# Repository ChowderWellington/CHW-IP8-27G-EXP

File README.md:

# CHW-IP8-27G-EXP
An open source inkjet color printer with a nozzle built from the ground up!
<div align="center"></div>

(Chowder Hardware Works-Inkjet Printer 8 Nozzle-27 gauge precision nozzles-experimental)

Printhead: PX8-20H-01

Manufacturer: Chowder INC

DPI: 1.5

yes i love naming things annoyingly

## Overview
The CHW-IP8-27G-EXP is an inkjet color printer that can print at really bad dpi! But it does work! and i'm not using other people's nozzles, as I built my own from scratch!

## Features
- Very replaceable (you can 3D print any non-electrical parts and to get replacements for any electrical stuff is very cheap!)
- Custom Nozzle

# Full CAD

Here are the .stp files (THEY NEED TO BE PRINTED SEPARATELY) because stardance doesn't like .stl's

[Nozzles+Manifold](https://github.com/ChowderWellington/CHW-IP8-27G-EXP/blob/main/cad/Main%20Nozzle%20Setup%20V4.5%20%2B%20Manifold.stp)

[Printhead](https://github.com/ChowderWellington/CHW-IP8-27G-EXP/blob/main/cad/Main%20printhead%20V1.stp)

If you would like to recreate what I have done, use these files, or check out the .stls below if you would prefer them

[Nozzles+Manifold](https://github.com/ChowderWellington/CHW-IP8-27G-EXP/blob/main/cad/Main%20Nozzle%20Setup%20V4.5%20%2B%20Manifold.stl)

[Printhead](https://github.com/ChowderWellington/CHW-IP8-27G-EXP/blob/main/cad/Main%20printhead%20V1.stl)

## Replacing parts (part of the Full CAD)

I know a lot of the parts may break, especially the nozzles which can be faulty, but you should be able to find replacement bits for almost anything below. These are all in stl format btw.

[Single Lid for nozzle](https://github.com/ChowderWellington/CHW-IP8-27G-EXP/blob/main/cad/Main%20Nozzle%20Setup%20V4.5%20Lid%20Single.stl)

[Single Tank for nozzle](https://github.com/ChowderWellington/CHW-IP8-27G-EXP/blob/main/cad/Main%20Nozzle%20Setup%20V4.5%20Tank%20Single.stl)

[Main Printhead](https://github.com/ChowderWellington/CHW-IP8-27G-EXP/blob/main/cad/Main%20printhead%20V1.stl)

[Manifold](https://github.com/ChowderWellington/CHW-IP8-27G-EXP/blob/main/cad/Manifold%20V1.stl)

## Older Models (part of the Full CAD)
Older models of most of the parts can be found in the [cad folder](https://github.com/ChowderWellington/CHW-IP8-27G-EXP/tree/main/cad). However, it is NOT recommended to use them. Please use the newest model (V4.5 for the nozzle, V1 for the printhead and V1 for the manifold). 

## How to print the printer (part of the Full CAD)

1. Download the relevant files from the model files section above
2. Print it on any 3D printer using supports. For the nozzle and the manifold, it should only generate supports for the piping. Not inside it. For the printhead, there should be no supports.
3. Assemble using the guide (W.I.P)

This project was fit for a Bambu Labs A1 Mini, and a 0.4MM nozzle, but I assume it will work on anything else.

## Technical details

The PX8-20H-01 contains 8 piezoelectric discs that move forward and backwards under high voltage, causing a membrane to push a tiny ink droplet out onto a page, hence the name - inkjet. A motor in the CHW-IP8-27G moves the PX8-20H-01 back and forth, meaning it can print anywhere on a page using its nozzles. It is 1.5 DPI 

## Model Names
- CHW-IP8-27G-EXP - Full printer assembly (Printhead, nozzles, feeders etc)
- PX8-20H-01 - Experimental nozzle (Newest model)

## Datasheets
- [PX8-20H-01](https://github.com/ChowderWellington/CHW-IP8-27G-EXP/blob/main/assets/PX8-20H-01%20DATASHEET.pdf)

## Logo

The logo was designed by me, and it has a pretty cool story! 

I was originally going for a cool spiral sort of logo, where i made a bunch of circles that get increasingly smaller and change between black and white, but in canva, I highlighted the centre circle, and noticed that the select box looked warped for some reason. It reminded me of [this](https://raw.githubusercontent.com/ChowderWellington/CHW-IP8-27G-EXP/refs/heads/main/assets/cafe-wall-big.gif) optical illusion so i just stuck with it, and now it is the logo!

## PCB
You can order the pcb from anywhere, but [here are the files you'll need](https://github.com/ChowderWellington/CHW-IP8-27G-EXP/tree/main/pcb)

You actually don't need most of these, just [the gerber files](https://github.com/ChowderWellington/CHW-IP8-27G-EXP/raw/refs/heads/main/pcb/Gerber_PX8-20H-01_PCB_PX8-20H-01_2026-08-30.zip) for manufacturing. To buy the parts you'll need to solder on to the board, check out the [BOM.csv](https://github.com/ChowderWellington/CHW-IP8-27G-EXP/blob/main/BOM.csv)

## Extra thanks!
- Thank you so much to stardance for funding whatever this is! Y'all are the best!! Please keep doing what you're doing, and everyone WILL enjoy it! 
- Also big thanks to YOUTUBE for hosting videos that i can watch to learn about printers (I knew nothing about them before this)
- Huge thanks to any teacher in my classroom that didn't tell me off for working on this during class time whoops

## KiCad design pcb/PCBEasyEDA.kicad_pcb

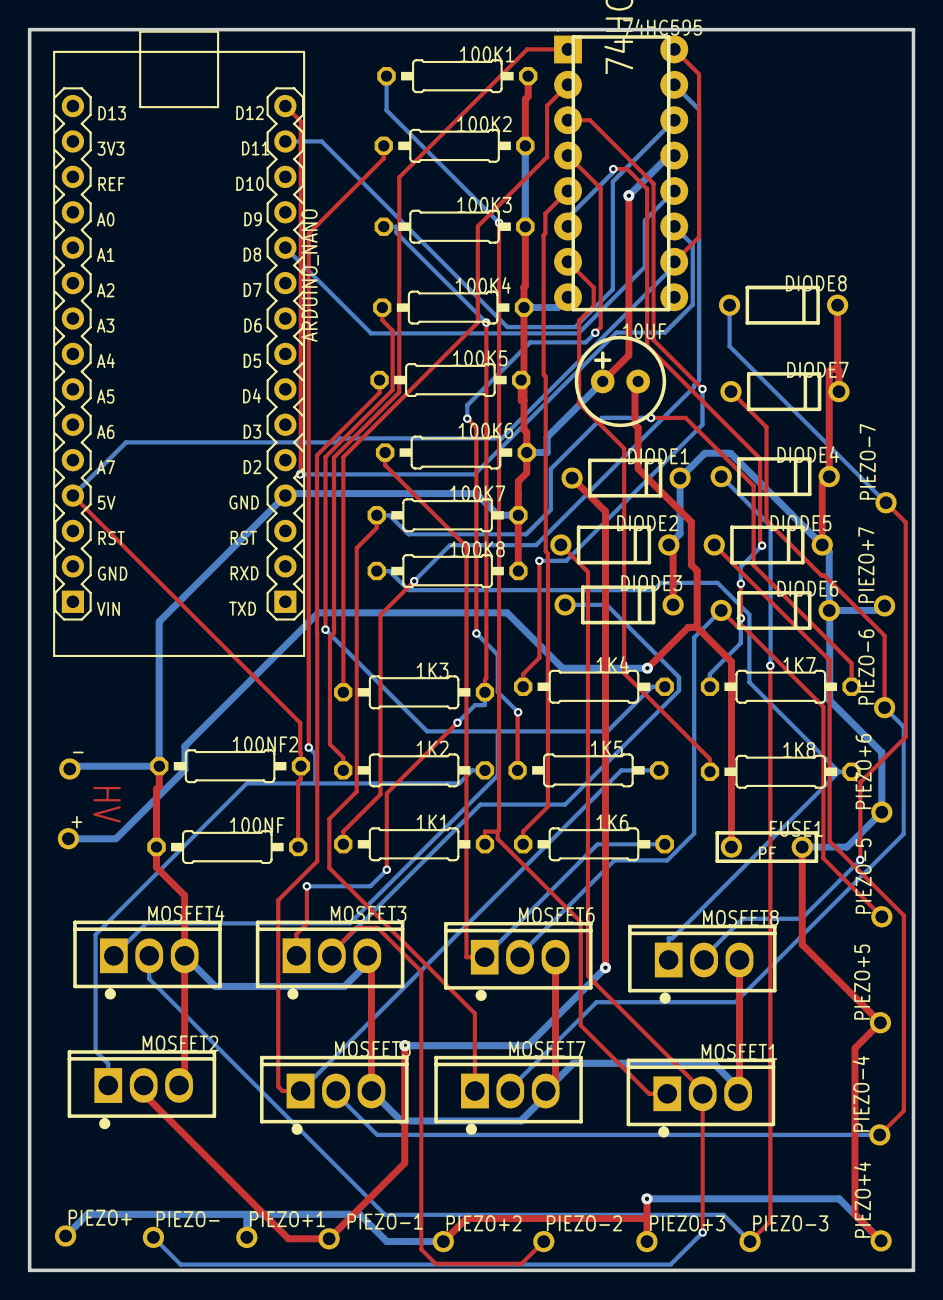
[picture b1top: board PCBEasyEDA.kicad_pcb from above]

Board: 2 copper layers, 63.4 x 89.0 mm, 56 parts (0 on the bottom side), 31 nets.

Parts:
1K1, 1K2, 1K3, 1K4, 1K5, 1K6, 1K7, 1K8: R-US_0207/10; 0207x10
10UF: 10uF; 10UF 100V
74HC595: 74HC595_; 74HC595
100K1, 100K2, 100K3, 100K4, 100K5, 100K6, 100K7, 100K8: 100K1; 0207x10
100NF, 100NF2: 100NF; 0207x10
+: +; THROUGHHOLEPIN
-: -; THROUGHHOLEPIN
ARDUINO_NANO: ARDUINO_NANO; COMM-TH_ARDUINO_NANO
DIODE1, DIODE2, DIODE3, DIODE4, DIODE5, DIODE6, DIODE7, DIODE8: 1N4007 (DO-41); 1N4007_(DO-41)
FUSE1: Polyfuse; POLYFUSE FOOTPRINT
MOSFET1, MOSFET2, MOSFET3, MOSFET4, MOSFET5, MOSFET6, MOSFET7, MOSFET8: IRL540NPBF-VB; TO-220AB-3_L10.4-W4.6-P2.54-L
PIEZO+, PIEZO+1, PIEZO+2, PIEZO+3, PIEZO+4, PIEZO+5, PIEZO+6, PIEZO+7: Piezo+; THROUGHHOLEPIN
PIEZO-, PIEZO-1, PIEZO-2, PIEZO-3, PIEZO-4, PIEZO-5, PIEZO-6, PIEZO-7: Piezo-; THROUGHHOLEPIN

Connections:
1K3_2: 1K3.2, 100K3.1, MOSFET3.1
1K4_2: 1K4.2, 100K4.1, MOSFET4.1
1K5_2: 1K5.2, 100K5.1, MOSFET5.1
1K6_2: 1K6.2, 100K6.1, MOSFET6.1
1K7_2: 1K7.2, 100K7.1, MOSFET7.1
1K8_2: 1K8.2, 100K8.1, MOSFET8.1
74HC595_1: 1K2.1, 74HC595.1
74HC595_2: 1K3.1, 74HC595.2
74HC595_3: 1K4.1, 74HC595.3
74HC595_4: 1K5.1, 74HC595.4
74HC595_5: 1K6.1, 74HC595.5
74HC595_6: 1K7.1, 74HC595.6
74HC595_7: 1K8.1, 74HC595.7
74HC595_15: 1K1.1, 74HC595.15
+_1: 10UF.2, +.1, FUSE1.1
ARDUINO_NANO_11: 74HC595.12, ARDUINO_NANO.11
ARDUINO_NANO_14: 74HC595.14, ARDUINO_NANO.14
ARDUINO_NANO_15: 74HC595.11, ARDUINO_NANO.15
DIODE4_A: DIODE4.A, MOSFET4.2, PIEZO-3.1
DIODE6_A: DIODE6.A, MOSFET6.2, PIEZO-5.1
DIODE8_A: DIODE8.A, MOSFET8.2, PIEZO-7.1
GND: 10UF.1, 74HC595.8, 74HC595.13, 100K1.2, 100K2.2, 100K3.2, 100K4.2, 100K5.2, 100K6.2, 100K7.2, 100K8.2, 100NF.1, 100NF2.1, -.1, ARDUINO_NANO.4, MOSFET1.3, MOSFET2.3, MOSFET3.3, MOSFET4.3, MOSFET5.3, MOSFET6.3, MOSFET7.3, MOSFET8.3
HV+: DIODE1.C, DIODE2.C, DIODE3.C, DIODE4.C, DIODE5.C, DIODE6.C, DIODE7.C, DIODE8.C, FUSE1.2, PIEZO+.1, PIEZO+1.1, PIEZO+2.1, PIEZO+3.1, PIEZO+4.1, PIEZO+5.1, PIEZO+6.1, PIEZO+7.1
MOSFET1_1: 1K1.2, 100K1.1, MOSFET1.1
MOSFET1_2: DIODE2.A, MOSFET1.2, PIEZO-.1
MOSFET2_1: 1K2.2, 100K2.1, MOSFET2.1
MOSFET3_2: DIODE3.A, MOSFET3.2, PIEZO-2.1
MOSFET5_2: DIODE5.A, MOSFET5.2, PIEZO-4.1
MOSFET7_2: DIODE7.A, MOSFET7.2, PIEZO-6.1
PIEZO-1_1: DIODE1.A, MOSFET2.2, PIEZO-1.1
VCC: 74HC595.10, 74HC595.16, 100NF.2, 100NF2.2, ARDUINO_NANO.27
